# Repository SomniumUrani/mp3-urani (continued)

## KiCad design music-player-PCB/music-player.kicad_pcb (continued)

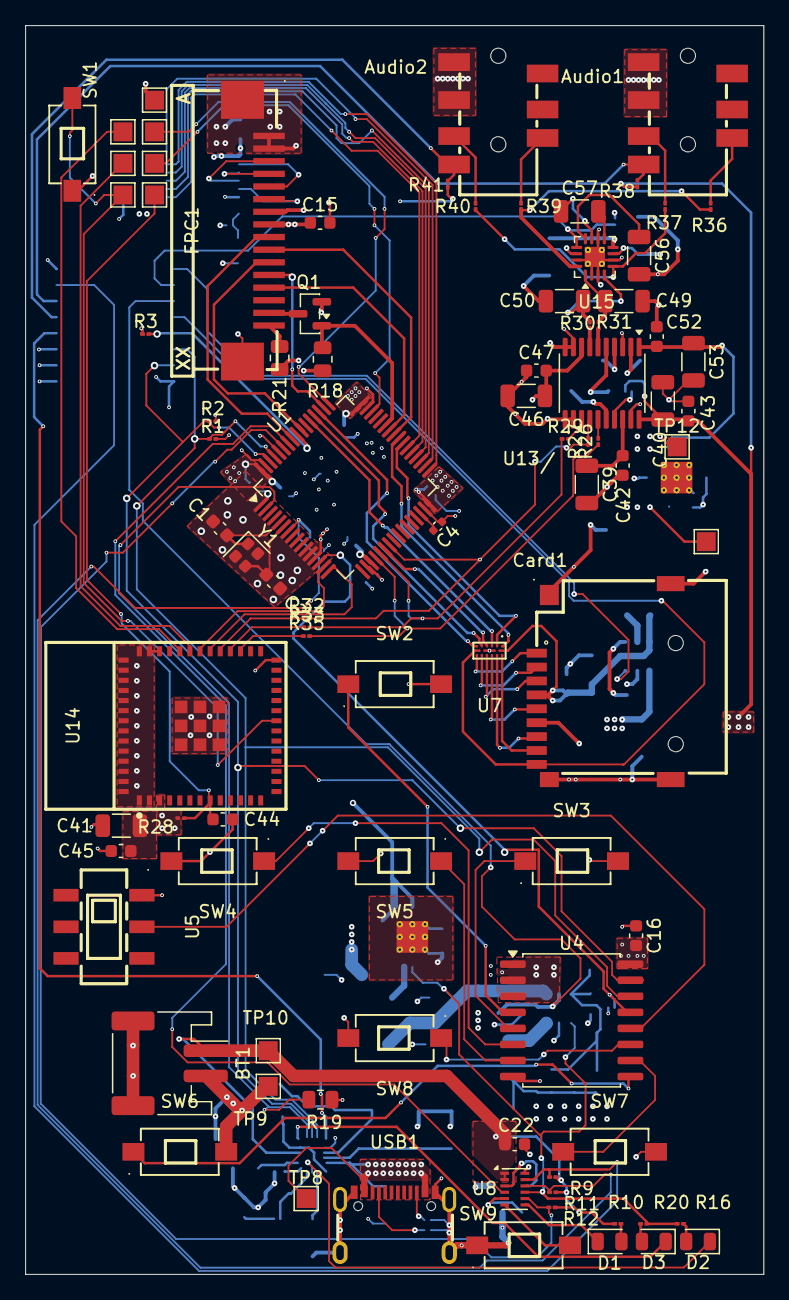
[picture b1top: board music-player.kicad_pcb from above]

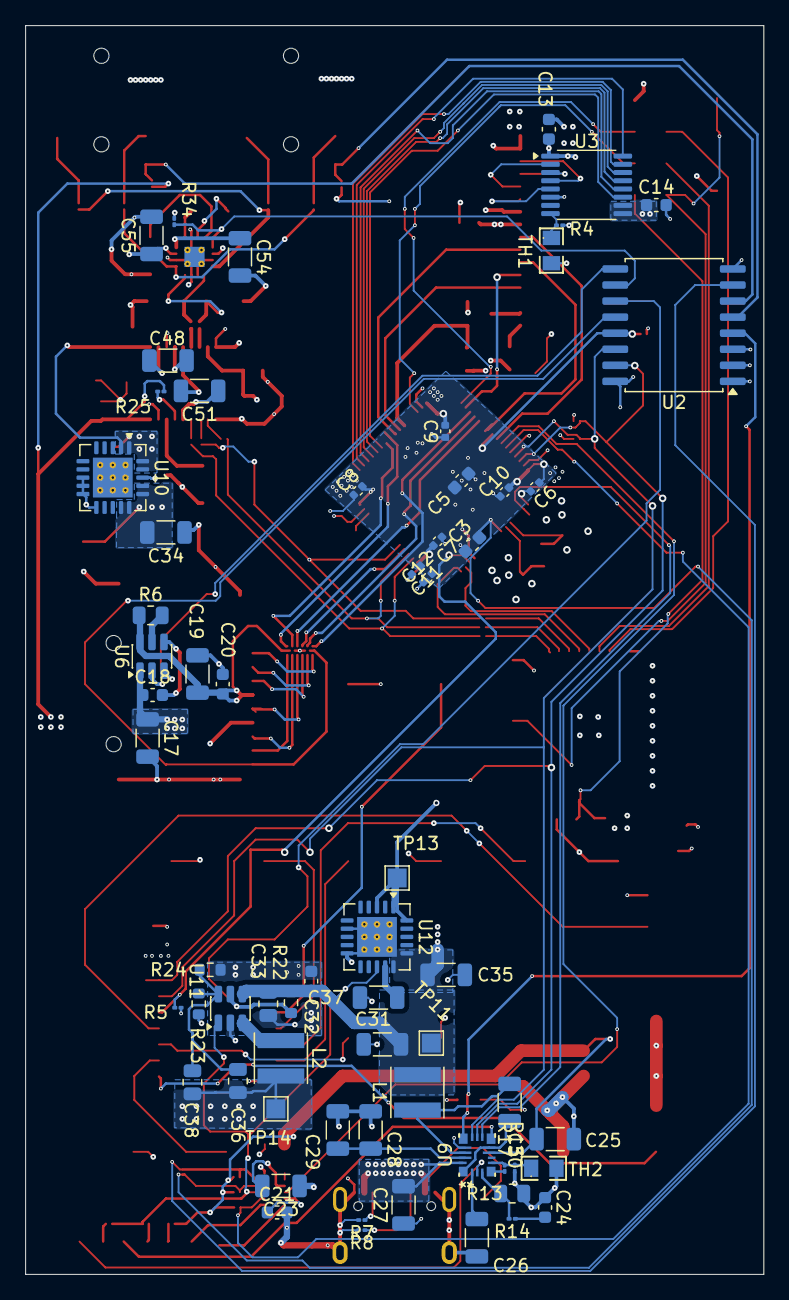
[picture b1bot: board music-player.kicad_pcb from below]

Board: 4 copper layers, 58.4 x 98.8 mm, 152 parts (64 on the bottom side), 127 nets.

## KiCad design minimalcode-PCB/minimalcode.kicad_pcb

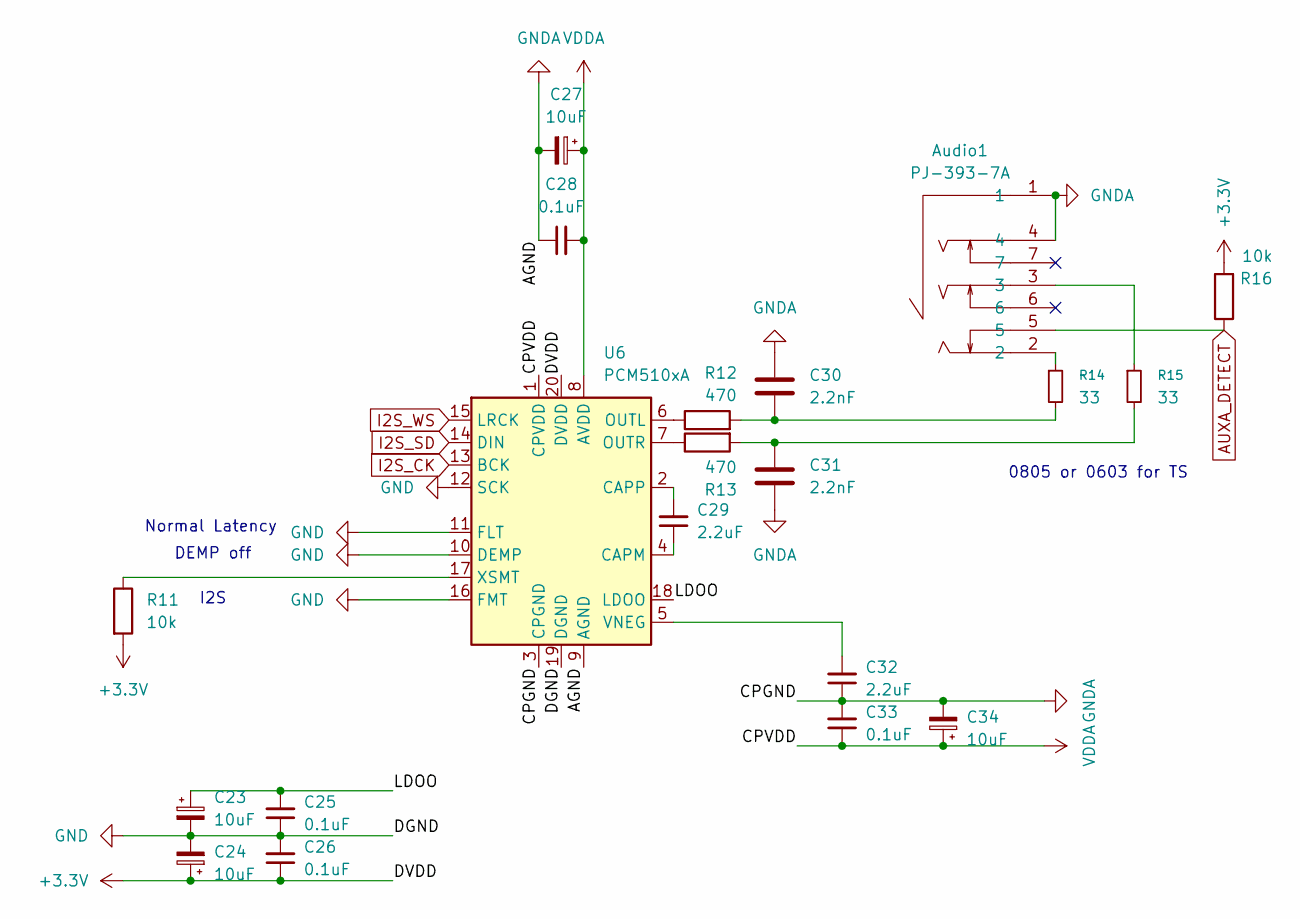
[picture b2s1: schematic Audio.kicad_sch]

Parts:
Audio1: PJ-393-7A; AUDIO-SMD_PJ-393-7A; MPN PJ-393-7A; LCSC Part C128990
C23, C24, C27, C34: 10uF; C_0603_1608Metric_Pad1.08x0.95mm_HandSolder
C25, C26, C28, C33: 0.1uF; C_0603_1608Metric_Pad1.08x0.95mm_HandSolder
C29, C32: 2.2uF; C_0603_1608Metric_Pad1.08x0.95mm_HandSolder
C30, C31: 2.2nF; C_0603_1608Metric_Pad1.08x0.95mm_HandSolder
R11, R16: 10k; R_0805_2012Metric
R12, R13: 470; R_0805_2012Metric
R14, R15: 33; R_0805_2012Metric
U6: PCM510xA; TSSOP-20_4.4x6.5mm_P0.65mm; LCSC Part C131154

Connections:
+3.3V: C24.1, C26.1, R11.2, R16.2, U6.20 (DVDD); also elsewhere on the board
/Audio/LDOO: C23.1, C25.2, U6.18 (LDOO)
AUXA_DETECT: Audio1.5, R16.1; also elsewhere on the board
GND: C23.2, C24.2, C25.1, C26.2, U6.10 (DEMP), U6.11 (FLT), U6.12 (SCK), U6.16 (FMT), U6.19 (DGND); also elsewhere on the board
GNDA: Audio1.1, Audio1.4, C27.2, C28.1, C30.1, C31.2, C32.1, C33.2, C34.2, U6.3 (CPGND), U6.9 (AGND)
I2S_CK: U6.13 (BCK); also elsewhere on the board
I2S_SD: U6.14 (DIN); also elsewhere on the board
I2S_WS: U6.15 (LRCK); also elsewhere on the board
unnamed: Audio1.2, R14.1
unnamed: Audio1.3, R15.1
unnamed: C30.2, R12.2, R14.2
unnamed: C31.1, R13.2, R15.2
unnamed: C29.1, U6.4 (CAPM)
unnamed: C29.2, U6.2 (CAPP)
unnamed: R12.1, U6.6 (OUTL)
unnamed: R13.1, U6.7 (OUTR)
unnamed: C32.2, U6.5 (VNEG)
unnamed: R11.1, U6.17 (XSMT)
VDDA: C27.1, C28.2, C33.1, C34.1, U6.1 (CPVDD), U6.8 (AVDD); also elsewhere on the board

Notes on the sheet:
0805 or 0603 for TS
I2S
DEMP off
Normal Latency

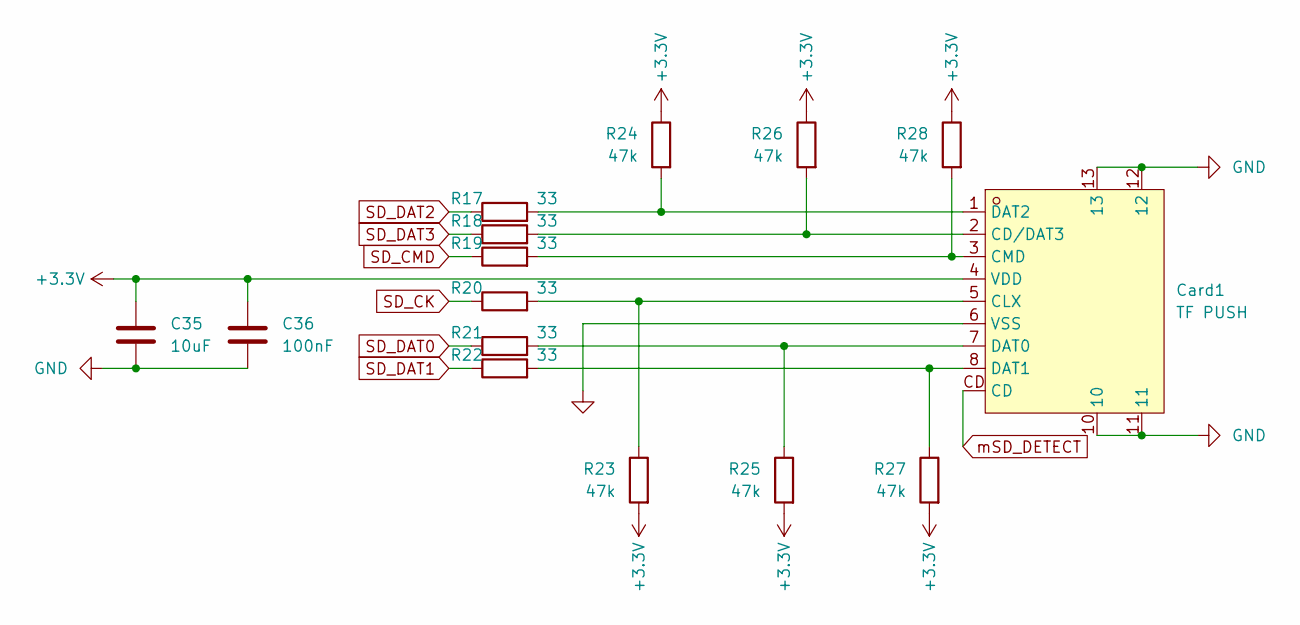
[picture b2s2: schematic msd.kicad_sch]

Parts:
C35: 10uF; C_0603_1608Metric_Pad1.08x0.95mm_HandSolder
C36: 100nF; C_0603_1608Metric_Pad1.08x0.95mm_HandSolder
Card1: TF PUSH; TF-SMD_TF-PUSH; MPN TF PUSH; LCSC Part C393941
R17, R18, R19, R20, R21, R22: 33; R_0805_2012Metric
R23, R24, R25, R26, R27, R28: 47k; R_0805_2012Metric

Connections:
+3.3V: C35.1, C36.1, Card1.4 (VDD), R23.2, R24.1, R25.2, R26.1, R27.2, R28.1; also elsewhere on the board
GND: C35.2, C36.2, Card1.6 (VSS), Card1.10, Card1.11, Card1.12, Card1.13; also elsewhere on the board
unnamed: Card1.2 (CD/DAT3), R18.2, R26.2
unnamed: Card1.5 (CLX), R20.2, R23.1
unnamed: Card1.3 (CMD), R19.2, R28.2
unnamed: Card1.7 (DAT0), R21.2, R25.1
unnamed: Card1.8 (DAT1), R22.2, R27.1
unnamed: Card1.1 (DAT2), R17.2, R24.2
SD_CK: R20.1; also elsewhere on the board
SD_CMD: R19.1; also elsewhere on the board
SD_DAT0: R21.1; also elsewhere on the board
SD_DAT1: R22.1; also elsewhere on the board
SD_DAT2: R17.1; also elsewhere on the board
SD_DAT3: R18.1; also elsewhere on the board
mSD_DETECT: Card1.CD; also elsewhere on the board

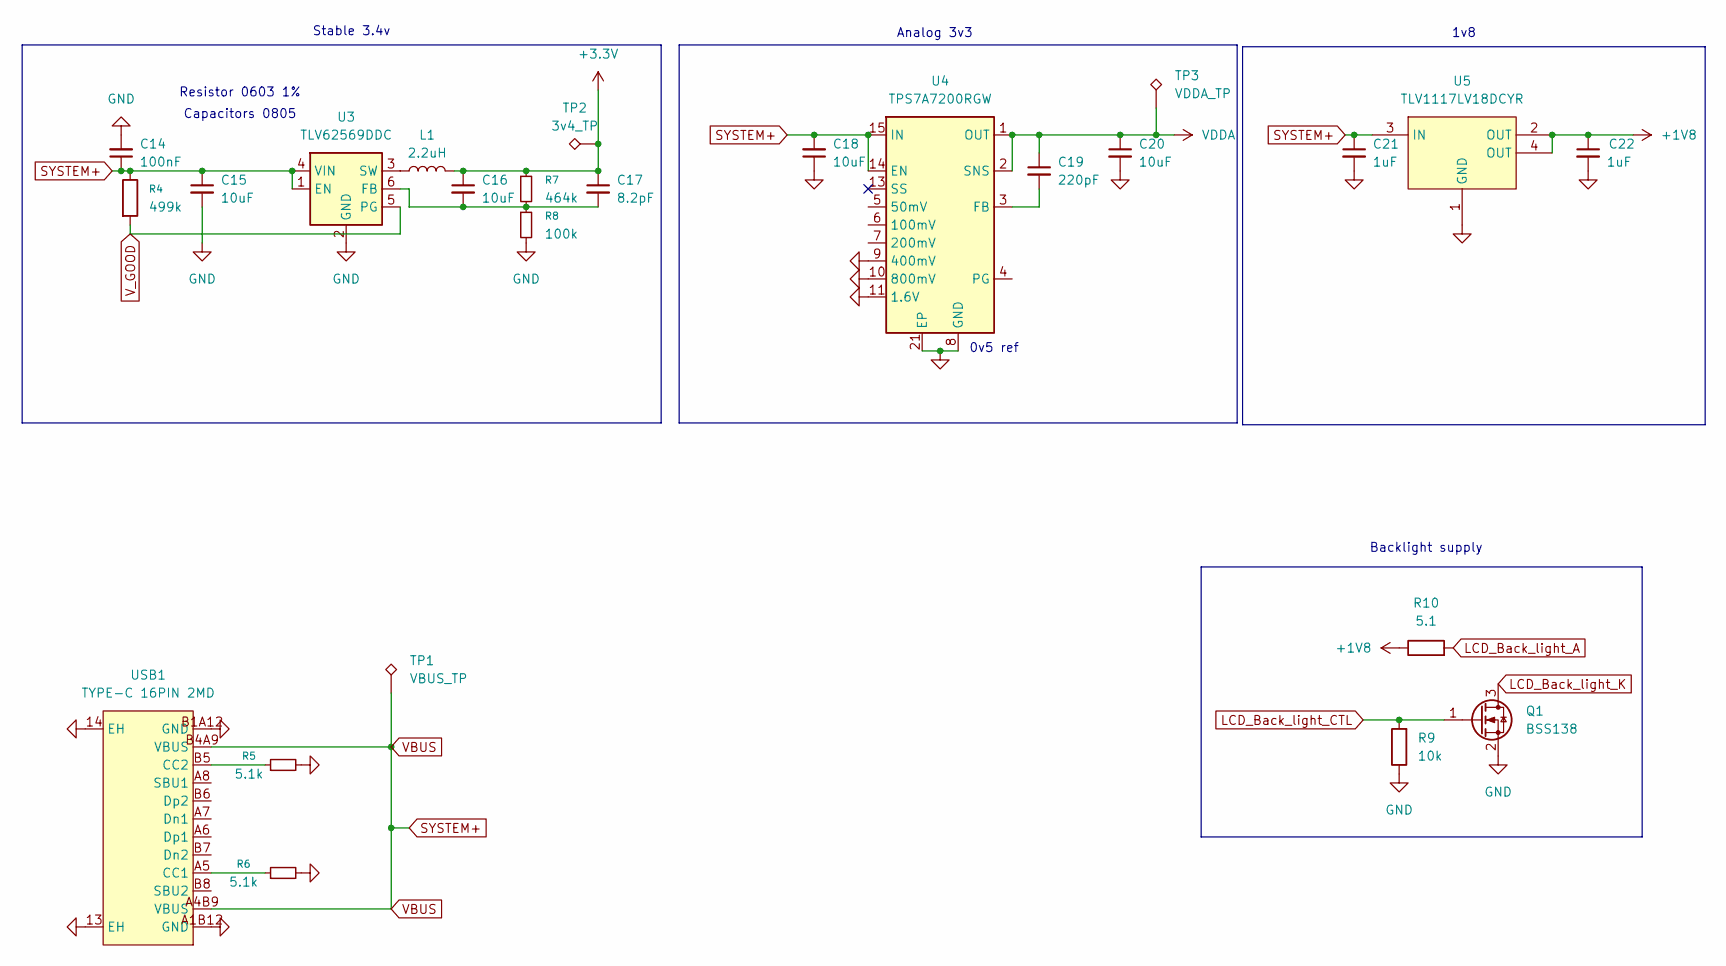
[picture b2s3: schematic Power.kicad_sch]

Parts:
C14: 100nF; C_0603_1608Metric_Pad1.08x0.95mm_HandSolder
C15, C16, C18, C20: 10uF; C_0603_1608Metric_Pad1.08x0.95mm_HandSolder
C17: 8.2pF; C_0603_1608Metric_Pad1.08x0.95mm_HandSolder; LCSC Part C1579
C19: 220pF; C_0603_1608Metric_Pad1.08x0.95mm_HandSolder
C21, C22: 1uF; C_0603_1608Metric_Pad1.08x0.95mm_HandSolder
L1: 2.2uH; L_Taiyo-Yuden_NR-40xx; LCSC Part C135262
Q1: BSS138; SOT-23
R4: 499k; R_0805_2012Metric
R5, R6: 5.1k; R_0805_2012Metric
R7: 464k; R_0805_2012Metric
R8: 100k; R_0805_2012Metric
R9: 10k; R_0805_2012Metric
R10: 5.1; R_0805_2012Metric
TP1: VBUS_TP; TestPoint_Pad_1.5x1.5mm
TP2: 3v4_TP; TestPoint_Pad_1.5x1.5mm
TP3: VDDA_TP; TestPoint_Pad_1.5x1.5mm
U3: TLV62569DDC; SOT-23-6; LCSC Part C141836
U4: TPS7A7200RGW; Texas_RGW0020A_VQFN-20-1EP_5x5mm_P0.65mm_EP3.15x3.15mm_Ther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
U5: TLV1117LV18DCYR; SOT-223-3_L6.5-W3.4-P2.30-LS7.0-BR; MPN TLV1117LV18DCYR; LCSC Part C80105
USB1: TYPE-C 16PIN 2MD; USB-C-SMD_TYPE-C-16PIN-2MD-073; MPN TYPE-C 16PIN 2MD(073); LCSC Part C2765186

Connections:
+1V8: C22.1, R10.1, U5.2 (OUT), U5.4 (OUT); also elsewhere on the board
+3.3V: C16.1, C17.1, L1.2, R7.1, TP2.1; also elsewhere on the board
GND: C14.2, C15.2, C18.1, C20.2, C21.2, C22.2, Q1.2 (S), R5.2, R6.2, R8.2, R9.1, U3.2 (GND), U4.8 (GND), U4.9 (400mV), U4.10 (800mV), U4.11 (1.6V), U4.18 (GND), U4.21 (EP), U5.1 (GND), USB1.13 (EH), USB1.14 (EH), USB1.A1B12 (GND), USB1.B1A12 (GND); also elsewhere on the board
LCD_Back_light_A: R10.2; also elsewhere on the board
LCD_Back_light_CTL: Q1.1 (G), R9.2; also elsewhere on the board
LCD_Back_light_K: Q1.3 (D); also elsewhere on the board
unnamed: C16.2, C17.2, R7.2, R8.1, U3.6 (FB)
unnamed: L1.1, U3.3 (SW)
unnamed: C19.2, U4.3 (FB)
unnamed: R6.1, USB1.A5 (CC1)
unnamed: R5.1, USB1.B5 (CC2)
SYSTEM+: C14.1, C15.1, C18.2, C21.1, R4.1, TP1.1, U3.1 (EN), U3.4 (VIN), U4.14 (EN), U4.15 (IN), U4.16 (IN), U4.17 (IN), U5.3 (IN), USB1.A4B9 (VBUS), USB1.B4A9 (VBUS); also elsewhere on the board
VDDA: C19.1, C20.1, TP3.1, U4.1 (OUT), U4.2 (SNS), U4.19 (OUT), U4.20 (OUT); also elsewhere on the board
V_GOOD: R4.2, U3.5 (PG)

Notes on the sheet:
Analog 3v3
Capacitors 0805
0v5 ref
Resistor 0603 1%
Stable 3.4v
1v8
Backlight supply

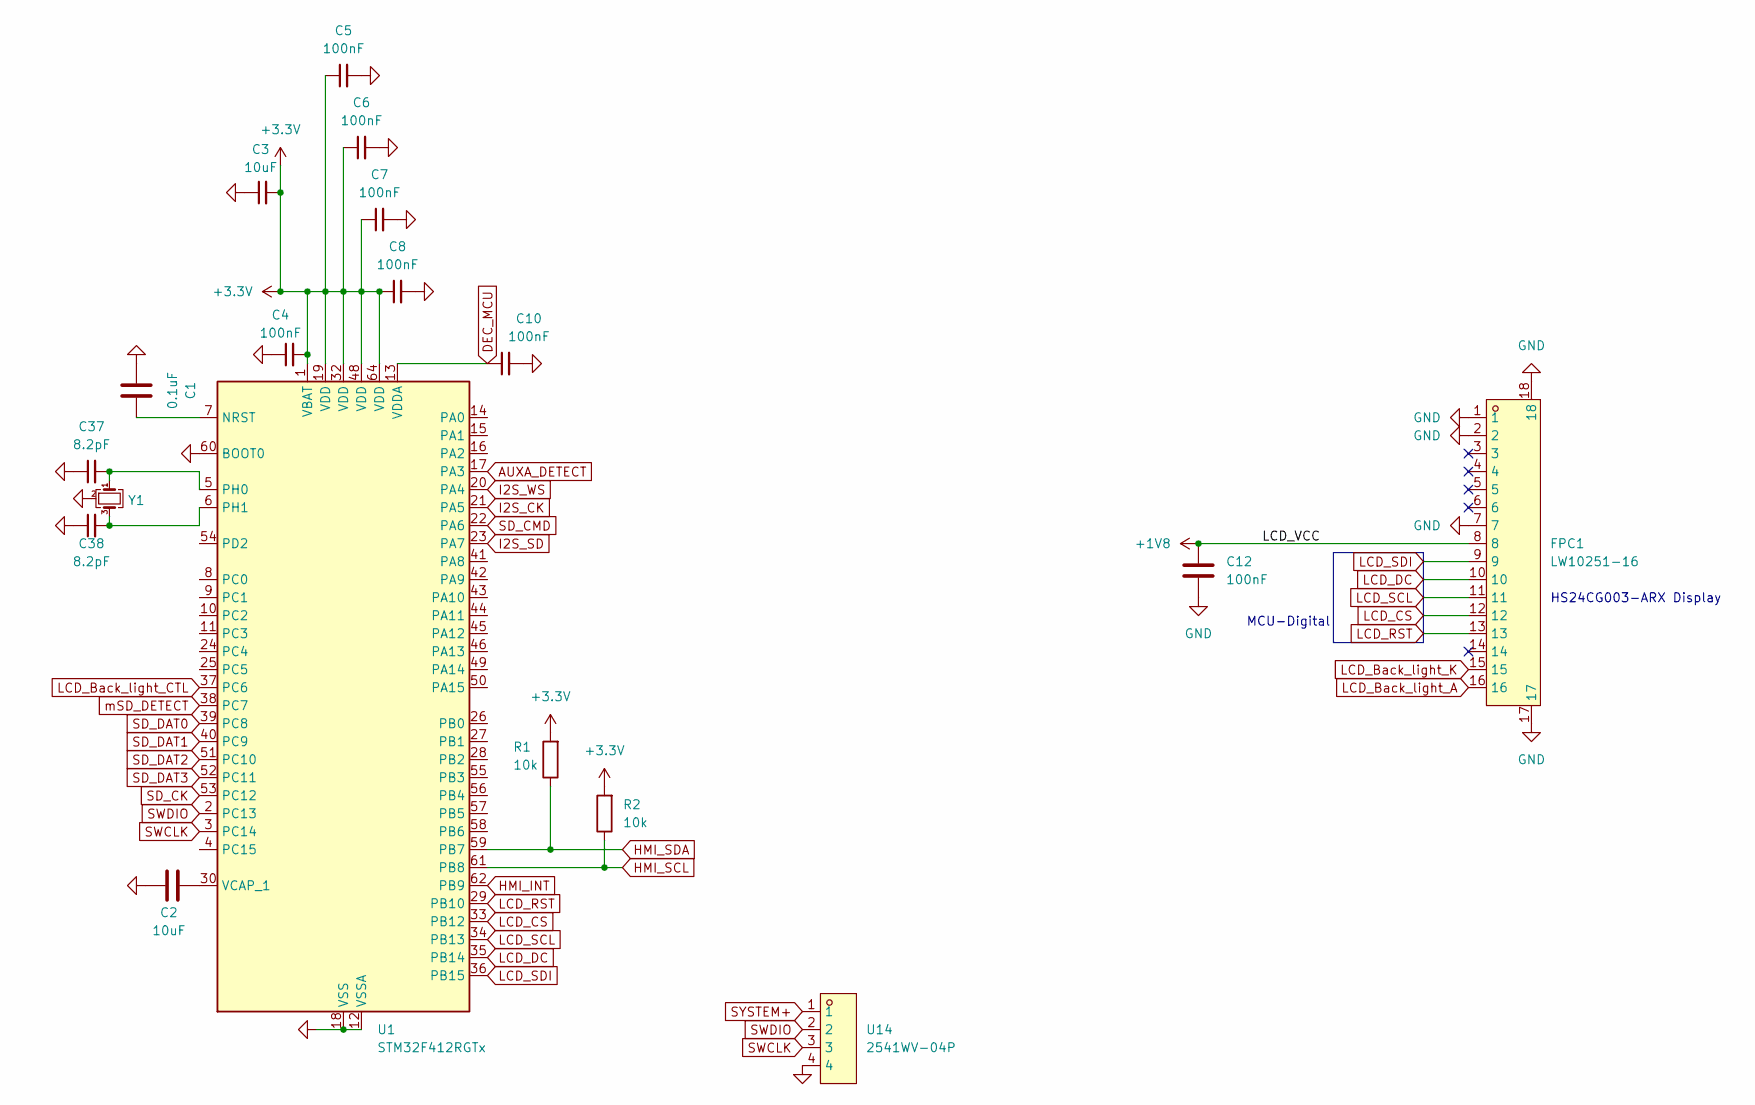
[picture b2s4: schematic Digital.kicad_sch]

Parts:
C1: 0.1uF; C_0603_1608Metric_Pad1.08x0.95mm_HandSolder
C2, C3: 10uF; C_0603_1608Metric_Pad1.08x0.95mm_HandSolder
C4, C5, C6, C7, C8, C10, C12: 100nF; C_0603_1608Metric_Pad1.08x0.95mm_HandSolder
C37, C38: 8.2pF; C_0402_1005Metric
FPC1: LW10251-16; FFC-SMD_16P-P01.00_LW10251-16; MPN LW10251-16; LCSC Part C375934
R1, R2: 10k; R_0805_2012Metric
U1: STM32F412RGTx; LQFP-64_10x10mm_P0.5mm; LCSC Part C2053691
U14: 2541WV-04P; HDR-TH_4P-P2.54-V-M-1; MPN 2541WV-04P; LCSC Part C5383113
Y1: 2.D.1.250000609; Crystal_SMD_2016-4Pin_2.0x1.6mm; LCSC Part C49867546

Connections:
+1V8: C12.1, FPC1.8; also elsewhere on the board
+3.3V: C3.2, C4.2, C5.1, C6.1, C7.1, C8.1, R1.2, R2.2, U1.1 (VBAT), U1.19 (VDD), U1.32 (VDD), U1.48 (VDD), U1.64 (VDD); also elsewhere on the board
AUXA_DETECT: U1.17 (PA3); also elsewhere on the board
DEC_MCU: C10.1, U1.13 (VDDA)
GND: C1.1, C2.1, C3.1, C4.1, C5.2, C6.2, C7.2, C8.2, C10.2, C12.2, C37.1, C38.1, FPC1.1, FPC1.2, FPC1.7, FPC1.17, FPC1.18, U1.12 (VSSA), U1.18 (VSS), U1.31 (VSS), U1.47 (VSS), U1.60 (BOOT0), U1.63 (VSS), U14.4, Y1.2 (G), Y1.4 (G); also elsewhere on the board
HMI_INT: U1.62 (PB9); also elsewhere on the board
HMI_SCL: R2.1, U1.61 (PB8); also elsewhere on the board
HMI_SDA: R1.1, U1.59 (PB7); also elsewhere on the board
I2S_CK: U1.21 (PA5); also elsewhere on the board
I2S_SD: U1.23 (PA7); also elsewhere on the board
I2S_WS: U1.20 (PA4); also elsewhere on the board
LCD_Back_light_A: FPC1.16; also elsewhere on the board
LCD_Back_light_CTL: U1.37 (PC6); also elsewhere on the board
LCD_Back_light_K: FPC1.15; also elsewhere on the board
LCD_CS: FPC1.12, U1.33 (PB12)
LCD_DC: FPC1.10, U1.35 (PB14)
LCD_RST: FPC1.13, U1.29 (PB10)
LCD_SCL: FPC1.11, U1.34 (PB13)
LCD_SDI: FPC1.9, U1.36 (PB15)
unnamed: C1.2, U1.7 (NRST)
unnamed: C37.2, U1.5 (PH0), Y1.1
unnamed: C38.2, U1.6 (PH1), Y1.3
unnamed: C2.2, U1.30 (VCAP_1)
SD_CK: U1.53 (PC12); also elsewhere on the board
SD_CMD: U1.22 (PA6); also elsewhere on the board
SD_DAT0: U1.39 (PC8); also elsewhere on the board
SD_DAT1: U1.40 (PC9); also elsewhere on the board
SD_DAT2: U1.51 (PC10); also elsewhere on the board
SD_DAT3: U1.52 (PC11); also elsewhere on the board
SWCLK: U1.3 (PC14), U14.3
SWDIO: U1.2 (PC13), U14.2
SYSTEM+: U14.1; also elsewhere on the board
mSD_DETECT: U1.38 (PC7); also elsewhere on the board

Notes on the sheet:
HS24CG003-ARX Display
MCU-Digital

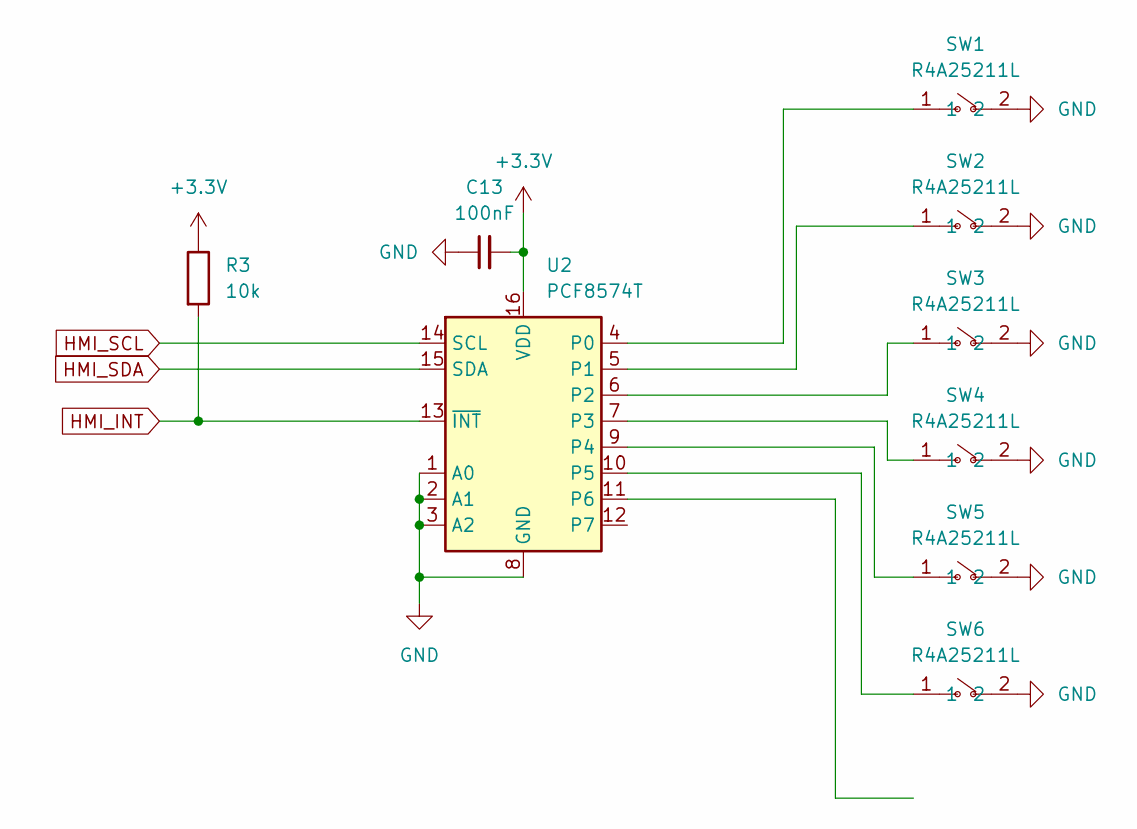
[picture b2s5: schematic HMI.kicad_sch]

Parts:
C13: 100nF; C_0603_1608Metric_Pad1.08x0.95mm_HandSolder
R3: 10k; R_0805_2012Metric
SW1, SW2, SW3, SW4, SW5, SW6: R4A25211L; SW-SMD_L6.0-W3.5-LS8.0-1; MPN R4A25211L; LCSC Part C49393629
U2: PCF8574T; SOIC-16W_7.5x10.3mm_P1.27mm; LCSC Part C53463892

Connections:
+3.3V: C13.2, R3.1, U2.16 (VDD); also elsewhere on the board
GND: C13.1, SW1.2, SW2.2, SW3.2, SW4.2, SW5.2, SW6.2, U2.1 (A0), U2.2 (A1), U2.3 (A2), U2.8 (GND); also elsewhere on the board
HMI_INT: R3.2, U2.13 (~INT); also elsewhere on the board
HMI_SCL: U2.14 (SCL); also elsewhere on the board
HMI_SDA: U2.15 (SDA); also elsewhere on the board
unnamed: SW1.1, U2.4 (P0)
unnamed: SW2.1, U2.5 (P1)
unnamed: SW3.1, U2.6 (P2)
unnamed: SW4.1, U2.7 (P3)
unnamed: SW5.1, U2.9 (P4)
unnamed: SW6.1, U2.10 (P5)

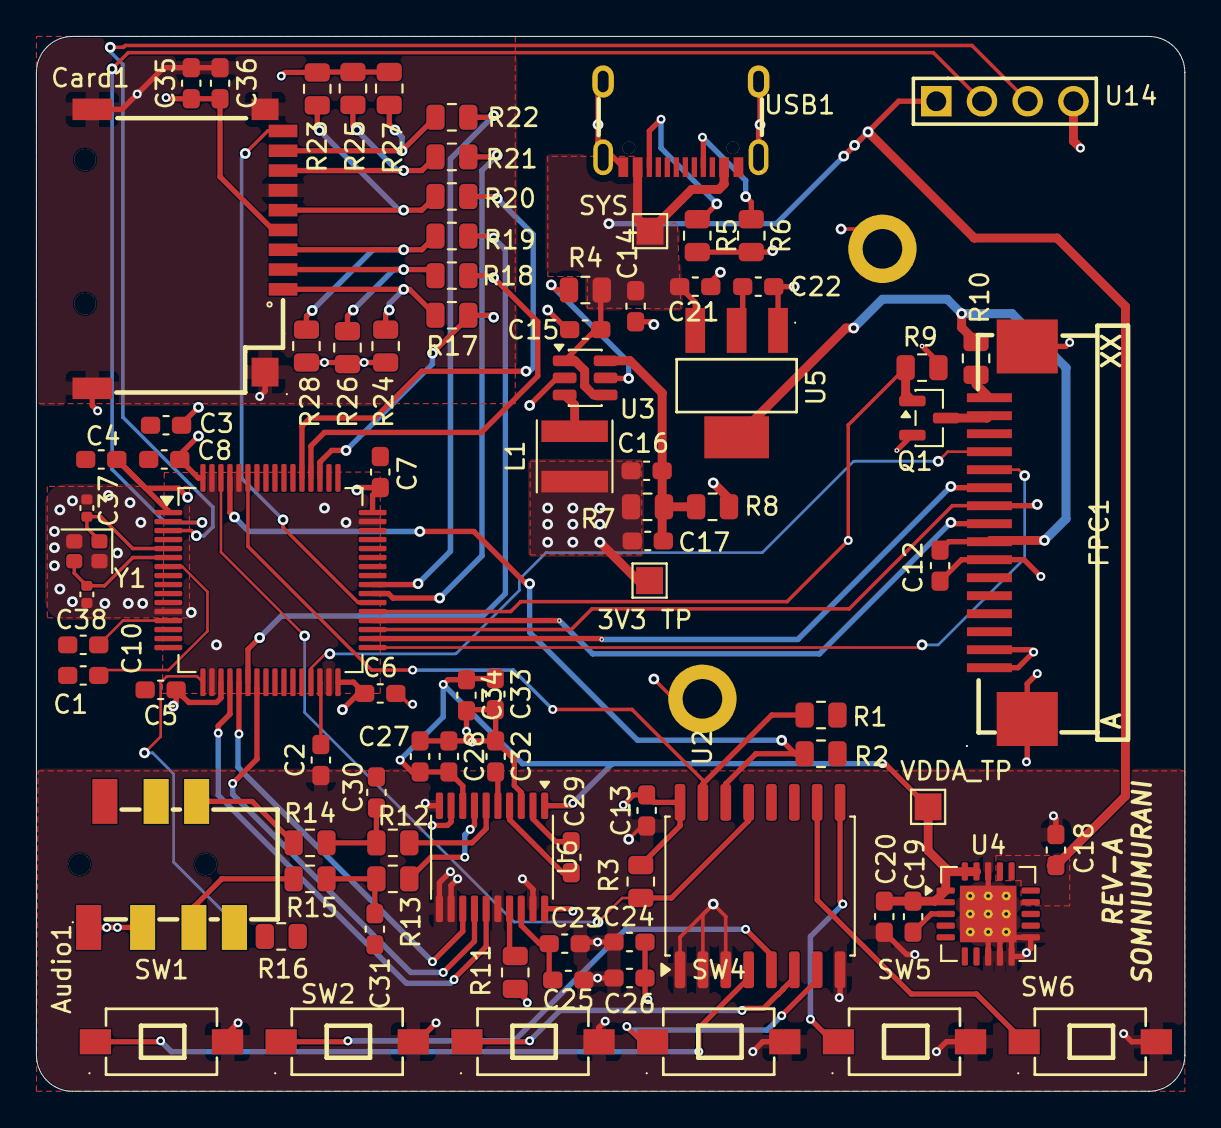
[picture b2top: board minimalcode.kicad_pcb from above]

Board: 4 copper layers, 63.8 x 58.6 mm, 87 parts (0 on the bottom side), 64 nets.

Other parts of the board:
3V3 TP: 3v4_TP; TestPoint_Pad_1.5x1.5mm
SYS: VBUS_TP; TestPoint_Pad_1.5x1.5mm
VDDA_TP: VDDA_TP; TestPoint_Pad_1.5x1.5mm

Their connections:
+3.3V: 3V3 TP.1 (1_1); also elsewhere on the board
SYSTEM+: SYS.1 (1_1); also elsewhere on the board
VDDA: VDDA_TP.1 (1_1); also elsewhere on the board

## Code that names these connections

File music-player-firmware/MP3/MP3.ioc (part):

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Mcu.Name=STM32F412C(E-G)Ux
Mcu.Package=UFQFPN48
Mcu.UserName=STM32F412CEUx
PA10.Mode=Simplex_Bidirectional_Master
PA10.Signal=SPI5_MOSI
PA11.Signal=GPIO_Input
PA13.Mode=Serial_Wire
PA13.Signal=SYS_JTMS-SWDIO
PA14.Mode=Serial_Wire
PA14.Signal=SYS_JTCK-SWCLK
PA15.Signal=GPIO_Analog
PA3.Signal=GPIO_Output
PA4.Signal=GPIO_Output
PA5.Mode=TX_Only_Simplex_Unidirect_Master
PA5.Signal=SPI1_SCK
PA6.Mode=SD_4_bits_Wide_bus
PA6.Signal=SDIO_CMD
PA7.Mode=TX_Only_Simplex_Unidirect_Master
PA7.Signal=SPI1_MOSI
PA8.Mode=SD_4_bits_Wide_bus
PA8.Signal=SDIO_D1
PA9.Mode=SD_4_bits_Wide_bus
PA9.Signal=SDIO_D2
PB0.Mode=Simplex_Bidirectional_Master
PB0.Signal=SPI5_SCK
PB1.Signal=GPIO_Output
PB12.Signal=GPXTI12
PB15.Mode=SD_4_bits_Wide_bus
PB15.Signal=SDIO_CK
PB2.Signal=GPIO_Output
PB4.Mode=SD_4_bits_Wide_bus
PB4.Signal=SDIO_D0
PB5.Mode=SD_4_bits_Wide_bus
PB5.Signal=SDIO_D3
PB7.Mode=I2C
PB7.Signal=I2C1_SDA
PB8.Mode=I2C
PB8.Signal=I2C1_SCL
PB9.Signal=GPXTI9
board=custom

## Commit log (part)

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2026-06-28 PCB: MCU essentials done
2026-06-29 Added LCD FPC connector
2026-06-30 PCB: changed to global labels
